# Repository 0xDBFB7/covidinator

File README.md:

# Update March 2021

Now shifted focus to purely electroporative effects. Please see

# [Pure electroporation](https://github.com/0xDBFB7/covidinator/releases/download/vx.x/pure_electroporation.pdf) 

Thanks!

---

Hi! Welcome! There's not a whole lot of real substance here, but maybe you'll find something useful. I hope you like it! 

This was a (in retrospect, misguided) project to determine if extremely high electric fields can produce mechanical stresses sufficient to break the viral membrane (so-called electroporation). This doesn't seem to be necessarily *completely* implausible, but it's sufficiently remote (and TRL 0) that I'm not super interested in continuing work on it given circumstances.

```
<3   <3   <3   <3   <3   <3   <3   <3   <3   <3   <3   <3   <3   <3 
```

# [Terse summary](https://github.com/0xDBFB7/covidinator/releases/download/vx.x/summary.pdf) 
# [Full paper with supplemental, unfinished](https://github.com/0xDBFB7/covidinator/releases/download/vx.x/paper.pdf)

## References & Resources [HTML](https://raw.githubusercontent.com/0xDBFB7/covidinator/master/documents/references.html) | [Zotero (categories!)](https://raw.githubusercontent.com/0xDBFB7/covidinator/master/documents/references.rdf) | [BiBTeX](https://raw.githubusercontent.com/0xDBFB7/covidinator/master/documents/references.bib) 

```
<:  ^_^  :>  ^_^  :>  ^_^  :>  ^_^  :>  ^_^  :>  ^_^  :>  ^_^  <:
```

Things that are here:

 * A cheap (~$300) synchronous photon counting fluorescence reader - just a crappy plate reader/Gel-Doc/spectroflurometer without the spectro- part. 
    - Can instantly quantify sub-nanogram quantities of dsDNA using Biotium GelGreen (Xu et al's fast phage titer sampling, score!).
 * Li et al's 600-picosecond avalanche transistor Marx pulser
 * A few microbiology protocols - E. coli and T4 bacteriophage.
 * A cheap (~$300) 6-12 GHz microwave absorption spectrometer / scalar network analyzer. Almost useless for small signals, does not provide the SNR required for biological purposes, don't build one.
    - firmware/eppenwolf/runs: Data from a number of data-taking runs of the Eppenwolf.
 * A wrapper around flaport/fdtd's awesome electromagnetics library:
    - tissue.py: supports import of IT.IS Foundation computational phantom voxel files, with their supplied Cole-Cole dielectric model, for tissue simulations. Pretty rough, not formally validated.
    - PCB.py: A test of coupled NGSPICE - adaptive timestep and direct KiCAD netlist import and probe/source creation. Currently totally broken.
 * biology/JAMES/ A bespoke MD program thanks to the not-invented-here syndrome. Not enough time was spent exploring GROMACS and LAMMPS features for bead-spring elastic models. A complete waste of time. There is zero reason for this to exist.
 * Reasonably bad note-taking. When all this is over I wanna make a real sweet lab notebook, the current offerings aren't, in my opinion, super great - suggestions for features and workflows are welcome!

```
<3   <3   <3   <3   <3   <3   <3   <3   <3   <3   <3   <3   <3   <3 
```

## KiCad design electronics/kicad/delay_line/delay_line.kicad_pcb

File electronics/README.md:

Milling settings:

30 degree carbide V-bit, 24 Krpm, 300 mm/min, 0.1 mm step-over, -0.1 mm step-down.

Check "Use aux. axis" in KiCAD gerber export, 

Todo: make a flatcam shell-file http://flatcam.org/manual/flatcamshell.html

G-code generated with FlatCAM, probed with Autoleveller 0.8.7 (bug in later versions),

then postprocessed with invert_probing.sh.

Board clamped to skim-cut MDF sheet and cut with regular scissors.

Paste stencils were laser cut from 80-weight black cardstock at 450 mm/min, 100%.

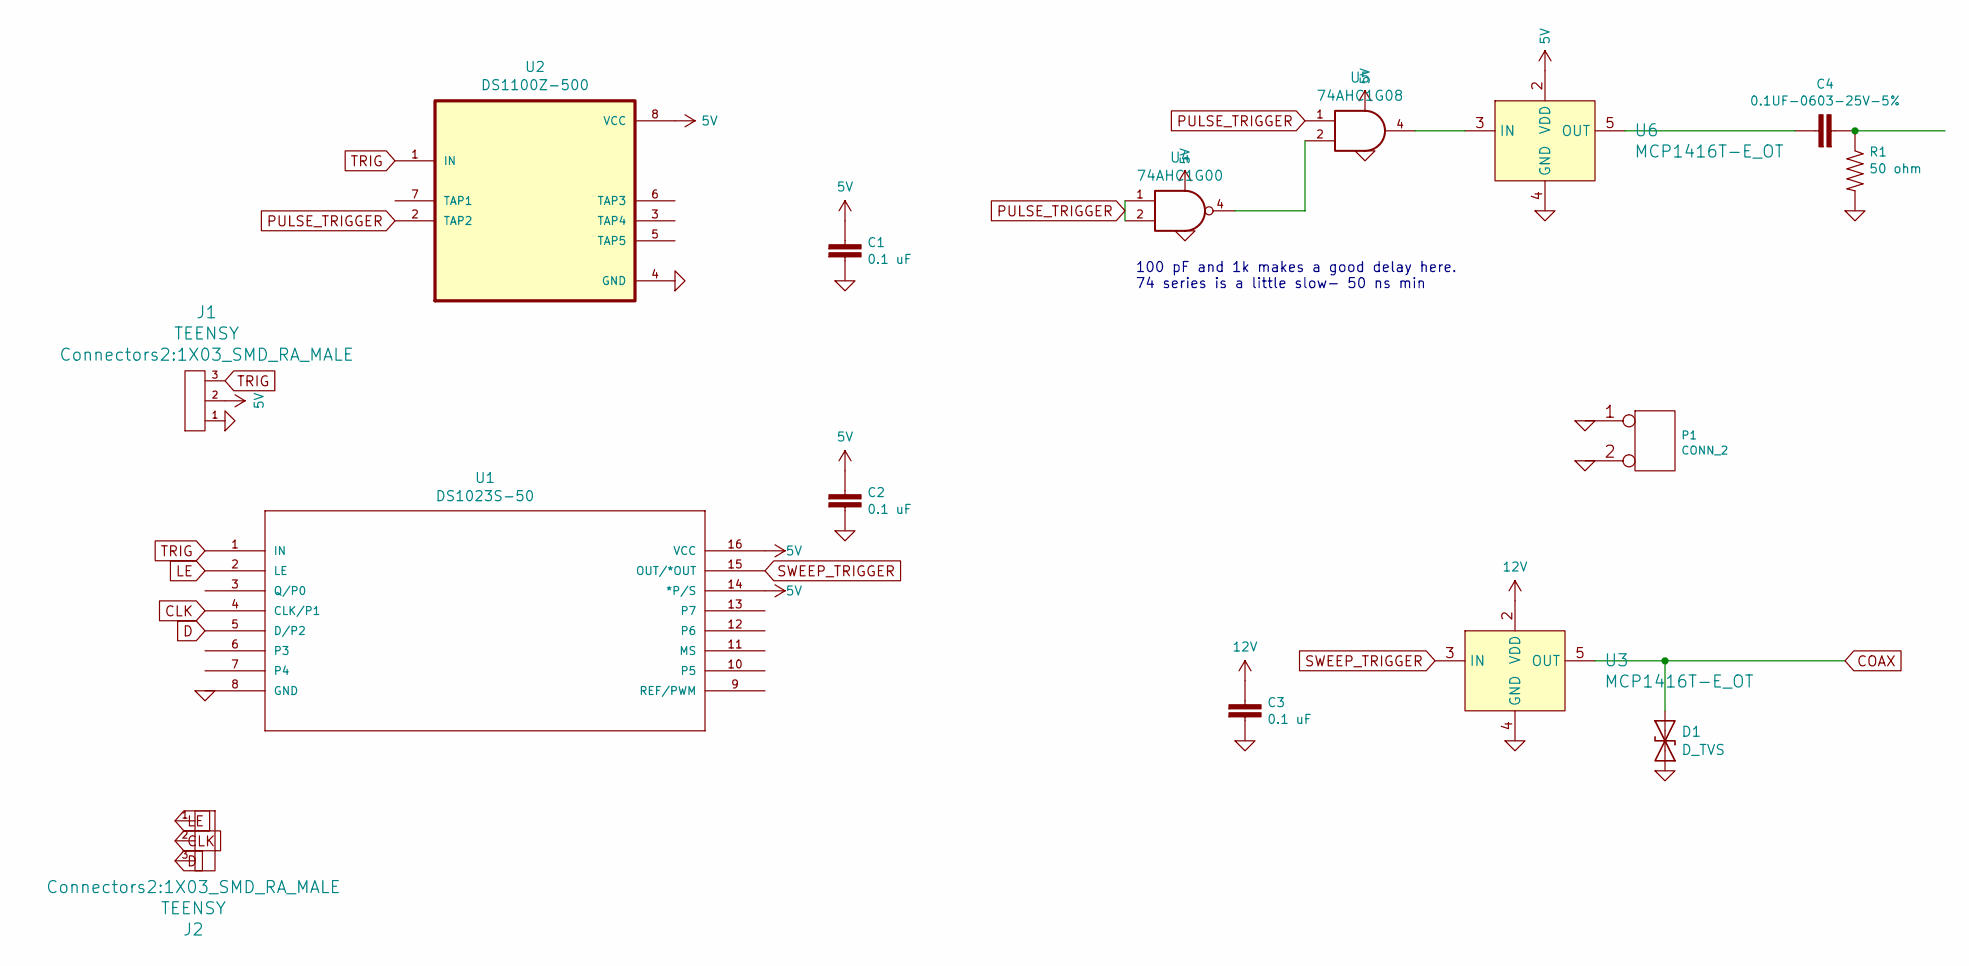
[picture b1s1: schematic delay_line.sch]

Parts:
C1, C2, C3: 0.1 uF; C_0603_1608Metric
C4: 0.1UF-0603-25V-5%; 0603
D1: D_TVS; D_SMA
J1, J2: TEENSY; 1X03_SMD_RA_MALE
P1: CONN_2; JUMPER_5102
R1: 50 ohm; 0805
U1: DS1023S-50; SOIC-16W_7.5x10.3mm_P1.27mm; MANUFACTURER_PART_NUMBER DS1023S50+
U2: DS1100Z-500; SOIC-8_3.9x4.9mm_P1.27mm
U3, U6: MCP1416T-E_OT; SOT-753; MPN MCP1416T-E/OT; Digi-Key_PN MCP1416T-E/OTCT-ND
U4: 74AHC1G00; SOT-23-5
U5: 74AHC1G08; SOT-23-5

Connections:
5V: C1.1, C2.1, J1.2, U1.14 (*P/S), U1.16 (VCC), U2.8 (VCC), U4.5 (VCC), U5.5 (VCC), U6.2 (VDD)
12V: C3.1, U3.2 (VDD)
CLK: J2.2, U1.4 (CLK/P1)
COAX: D1.1 (A1), U3.5 (OUT)
D: J2.3, U1.5 (D/P2)
GND: C1.2, C2.2, C3.2, D1.2 (A2), J1.1, P1.1, P1.2 (PM), R1.2, U1.8 (GND), U2.4 (GND), U3.4 (GND), U4.3 (GND), U5.3 (GND), U6.4 (GND)
LE: J2.1, U1.2 (LE)
unnamed: C4.1, U6.5 (OUT)
unnamed: C4.2, R1.1
unnamed: U4.4, U5.2
unnamed: U5.4, U6.3 (IN)
PULSE_TRIGGER: U2.2 (TAP2), U4.1, U4.2, U5.1
SWEEP_TRIGGER: U1.15 (OUT/*OUT), U3.3 (IN)
TRIG: J1.3, U1.1 (IN), U2.1 (IN)

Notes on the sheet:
100 pF and 1k makes a good delay here. 74 series is a little slow- 50 ns min

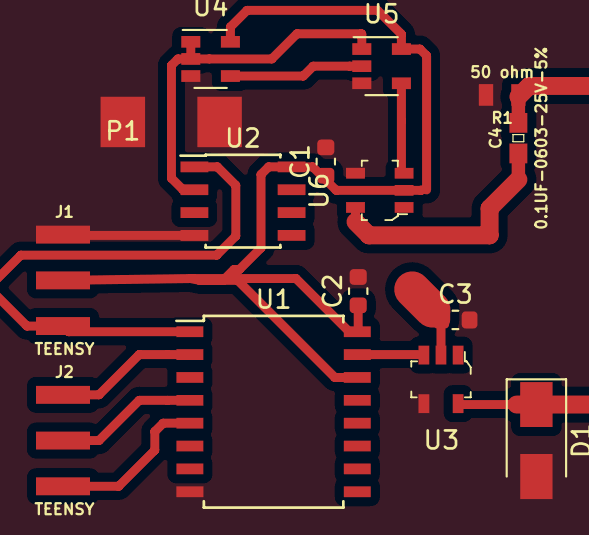
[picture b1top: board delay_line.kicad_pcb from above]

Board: 2 copper layers, 15 parts (0 on the bottom side), 14 nets.

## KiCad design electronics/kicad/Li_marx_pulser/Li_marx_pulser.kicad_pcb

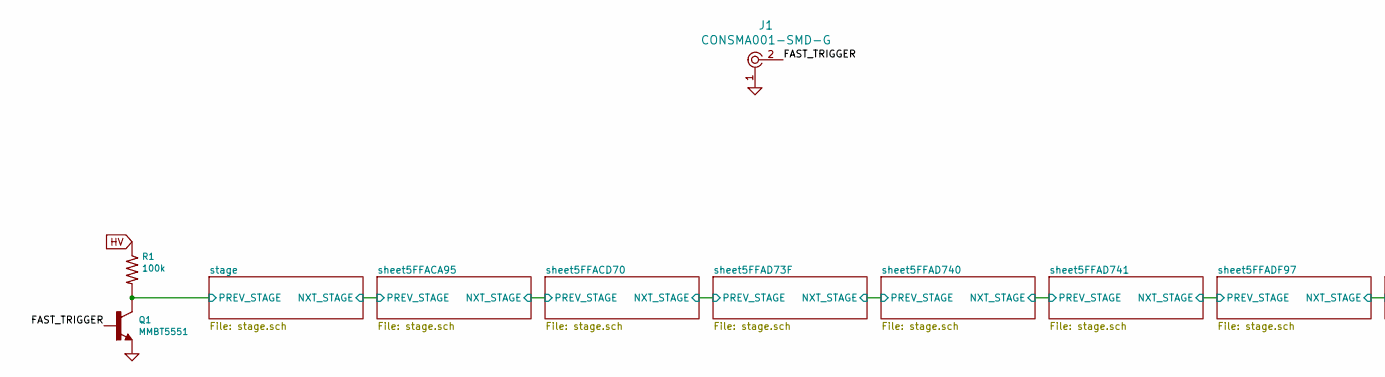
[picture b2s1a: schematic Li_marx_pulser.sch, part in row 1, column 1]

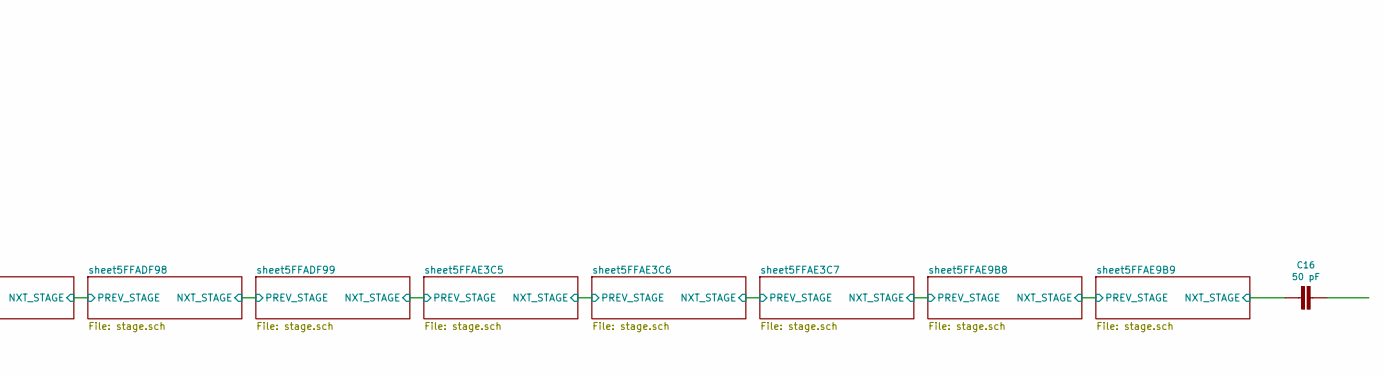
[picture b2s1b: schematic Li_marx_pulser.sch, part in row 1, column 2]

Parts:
C16: 50 pF; 1206
J1: CONSMA001-SMD-G; RF_SMA_Receptical_Vertical_CONSMA001-SMD-G; MPN CONSMA001-SMD-G; Digi-Key_PN CONSMA001-SMD-G-ND
Q1: MMBT5551; SOT23-3
R1: 100k; R_2512_6332Metric

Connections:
/FAST_TRIGGER: J1.2, Q1.1 (B)
/sheet5FFAE9B9/NXT_STAGE: C16.2; also elsewhere on the board
/stage/PREV_STAGE: Q1.3 (C), R1.2; also elsewhere on the board
GND: J1.1, Q1.2 (E); also elsewhere on the board
HV: R1.1; also elsewhere on the board

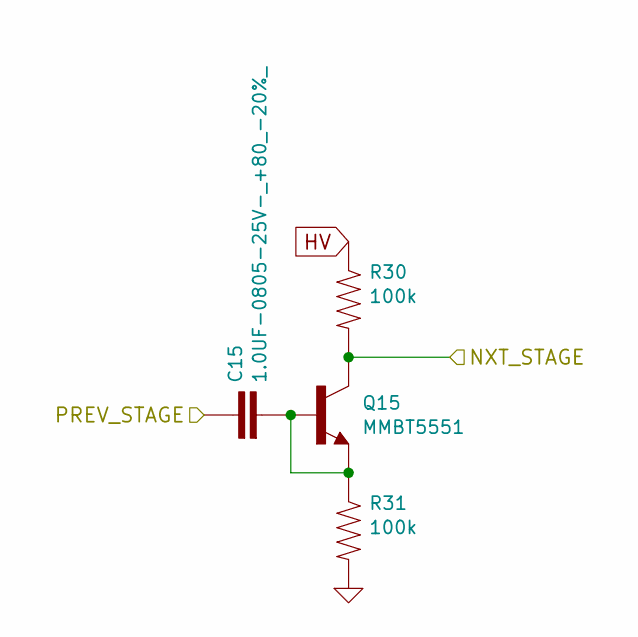
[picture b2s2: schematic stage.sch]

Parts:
C2: 1.0UF-0805-25V-_+80_-20%_; 1111(2828)
Q2: MMBT5551; SOT23-3
R4, R5: 100k; R_2512_6332Metric

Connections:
/stage/NXT_STAGE: Q2.3 (C), R4.2; also elsewhere on the board
/stage/PREV_STAGE: C2.1; also elsewhere on the board
GND: R5.2; also elsewhere on the board
HV: R4.1; also elsewhere on the board
unnamed: C2.2, Q2.1 (B), Q2.2 (E), R5.1

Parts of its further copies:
C3, C4, C5, C6, C7, C8, C9, C10, C11, C12, C13, C14, C15: 1.0UF-0805-25V-_+80_-20%_; 1111(2828)
Q3, Q4, Q5, Q6, Q7, Q8, Q9, Q10, Q11, Q12, Q13, Q14, Q15: MMBT5551; SOT23-3
R6, R7, R8, R9, R10, R11, R12, R13, R14, R15, R16, R17, R18, R19, R20, R21, R22, R23, R24, R25, R26, R27, R28, R29, R30, R31: 100k; R_2512_6332Metric

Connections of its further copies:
/sheet5FFACA95/NXT_STAGE: C4.1, Q3.3 (C), R6.2
/sheet5FFACD70/NXT_STAGE: C5.1, Q4.3 (C), R8.2
/sheet5FFAD73F/NXT_STAGE: C6.1, Q5.3 (C), R10.2
/sheet5FFAD740/NXT_STAGE: C7.1, Q6.3 (C), R12.2
/sheet5FFAD741/NXT_STAGE: C8.1, Q7.3 (C), R14.2
/sheet5FFADF97/NXT_STAGE: C9.1, Q8.3 (C), R16.2
/sheet5FFADF98/NXT_STAGE: C10.1, Q9.3 (C), R18.2
/sheet5FFADF99/NXT_STAGE: C11.1, Q10.3 (C), R20.2
/sheet5FFAE3C5/NXT_STAGE: C12.1, Q11.3 (C), R22.2
/sheet5FFAE3C6/NXT_STAGE: C13.1, Q12.3 (C), R24.2
/sheet5FFAE3C7/NXT_STAGE: C14.1, Q13.3 (C), R26.2
/sheet5FFAE9B8/NXT_STAGE: C15.1, Q14.3 (C), R28.2
/sheet5FFAE9B9/NXT_STAGE: Q15.3 (C), R30.2; also elsewhere on the board
/stage/NXT_STAGE: C3.1; also elsewhere on the board
GND: R7.2, R9.2, R11.2, R13.2, R15.2, R17.2, R19.2, R21.2, R23.2, R25.2, R27.2, R29.2, R31.2; also elsewhere on the board
HV: R6.1, R8.1, R10.1, R12.1, R14.1, R16.1, R18.1, R20.1, R22.1, R24.1, R26.1, R28.1, R30.1; also elsewhere on the board
unnamed: C3.2, Q3.1 (B), Q3.2 (E), R7.1
unnamed: C4.2, Q4.1 (B), Q4.2 (E), R9.1
unnamed: C5.2, Q5.1 (B), Q5.2 (E), R11.1
unnamed: C6.2, Q6.1 (B), Q6.2 (E), R13.1
unnamed: C7.2, Q7.1 (B), Q7.2 (E), R15.1
unnamed: C8.2, Q8.1 (B), Q8.2 (E), R17.1
unnamed: C9.2, Q9.1 (B), Q9.2 (E), R19.1
unnamed: C10.2, Q10.1 (B), Q10.2 (E), R21.1
unnamed: C11.2, Q11.1 (B), Q11.2 (E), R23.1
unnamed: C12.2, Q12.1 (B), Q12.2 (E), R25.1
unnamed: C13.2, Q13.1 (B), Q13.2 (E), R27.1
unnamed: C14.2, Q14.1 (B), Q14.2 (E), R29.1
unnamed: C15.2, Q15.1 (B), Q15.2 (E), R31.1

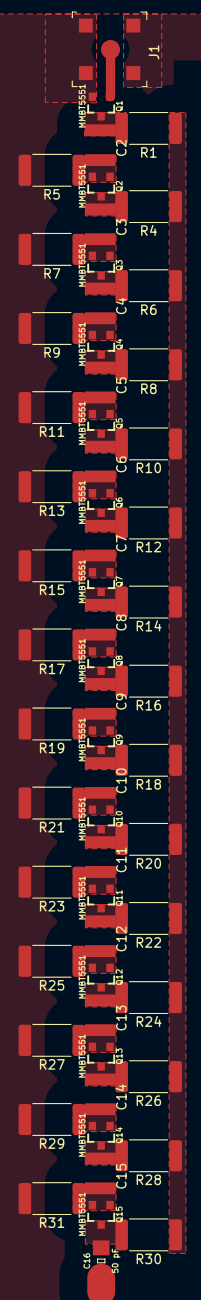
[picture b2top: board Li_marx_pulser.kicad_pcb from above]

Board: 2 copper layers, 60 parts (0 on the bottom side), 32 nets.

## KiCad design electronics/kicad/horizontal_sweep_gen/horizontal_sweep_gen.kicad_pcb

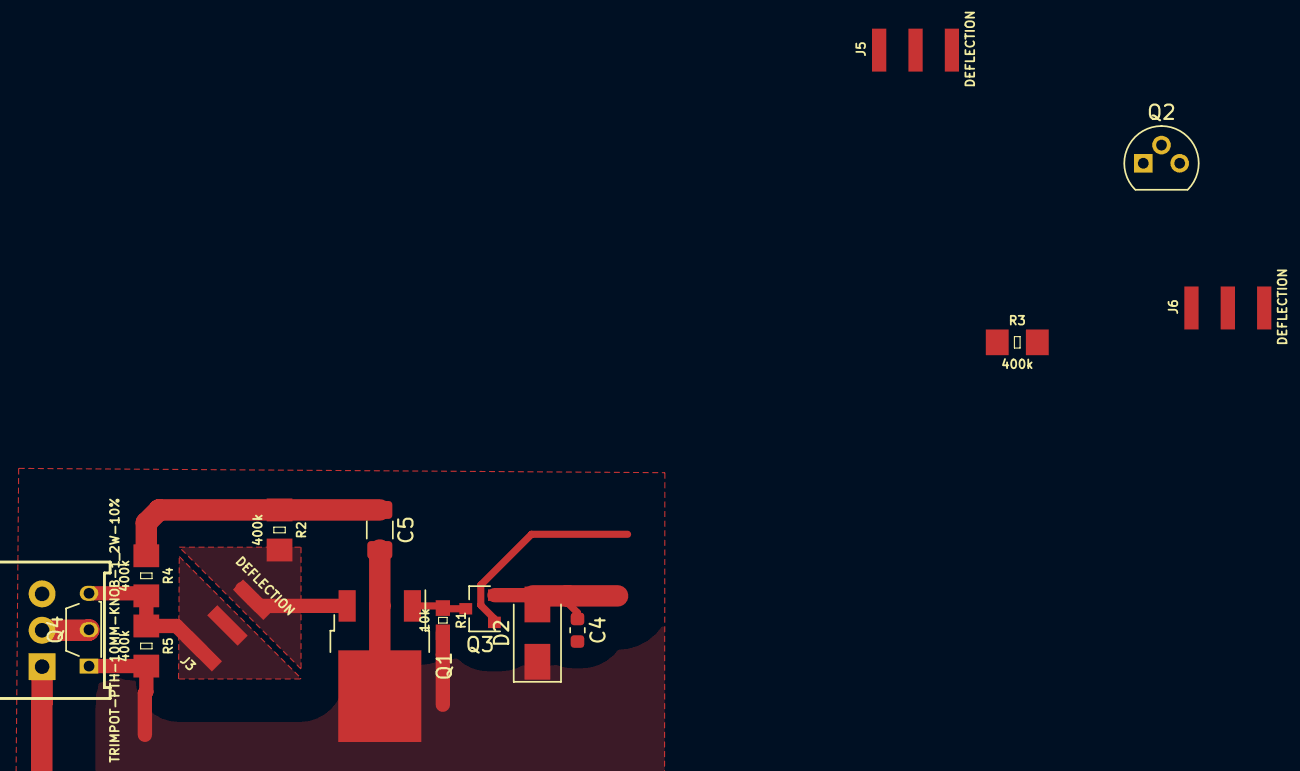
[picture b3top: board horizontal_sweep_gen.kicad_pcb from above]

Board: 2 copper layers, 16 parts (0 on the bottom side), 8 nets.

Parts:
C4: 0.1 uF; C_0603_1608Metric
C5: 50 pF; C_1206_3216Metric
D2: D_TVS; D_SMA
J3, J5, J6: DEFLECTION; 1X03_SMD_RA_MALE
Q1: TSM2N100CHC5G; TO-252-3_TabPin2
Q2: ZTX458; TO-92
Q3: BSS84; SOT-23
Q4: ZTX458; TO-92S_Wide
R1: 10k; 0603
R2, R3, R4, R5: 400k; 1206
VR1: TRIMPOT-PTH-10MM-KNOB-1_2W-10%; TRIMPOT-PTH-3386U

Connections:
GND: C4.2, C5.2, D2.1, Q1.2, Q2.1, Q4.1, R1.2, R5.2
HV: C5.1, R2.1, R4.1
HV_CENTER: J3.1, J3.2, Q4.3, R4.2, R5.1
unnamed: J5.1, Q2.3, R3.2
unnamed: Q1.1, Q3.3, R1.1
unnamed: Q4.2, VR1.2
SWEEP: J3.3, Q1.3, R2.2
VSWEEP_SLOPE: C4.1, D2.2, J6.1, Q3.2

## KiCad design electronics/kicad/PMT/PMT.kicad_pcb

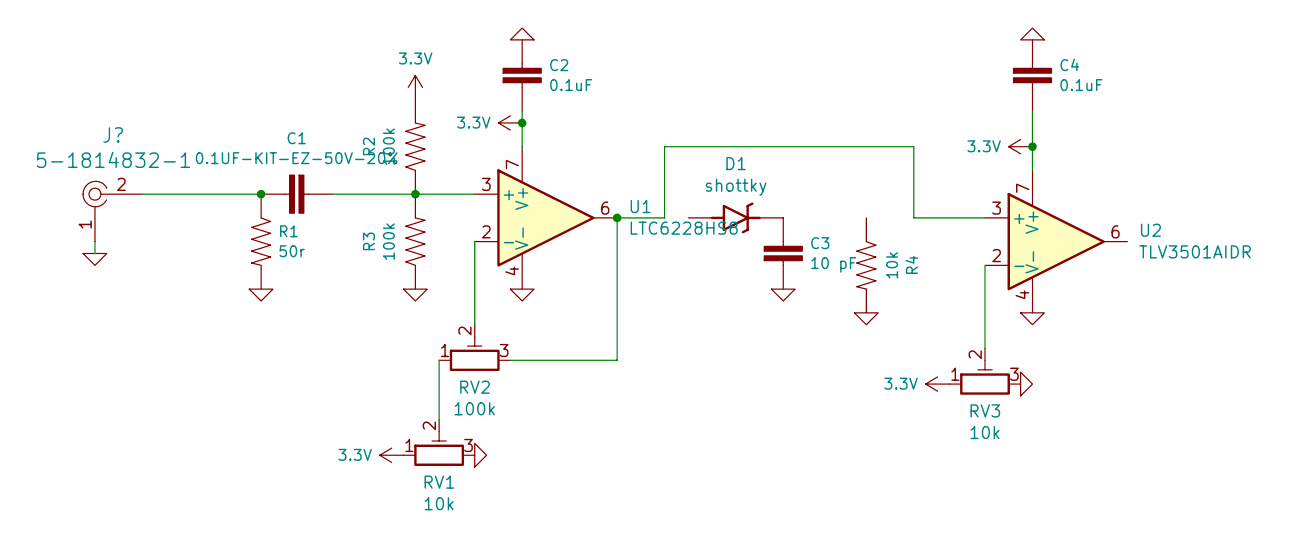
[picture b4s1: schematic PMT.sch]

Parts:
C1: 0.1UF-KIT-EZ-50V-20%; CAP-PTH-SMALL-KIT
C2, C4: 0.1uF; CAP-PTH-SMALL-KIT
C3: 10 pF; CAP-PTH-SMALL-KIT
D1: shottky; SMA-DIODE
R1: 50r; AXIAL-0.3
R2, R3: 100k; AXIAL-0.3
R4: 10k; AXIAL-0.3
RV1, RV3: 10k; PinHeader_1x03_P2.54mm_Vertical
RV2: 100k; PinHeader_1x03_P2.54mm_Vertical
U1: LTC6228HS8; DIP-8_W7.62mm
U2: TLV3501AIDR; DIP-8_W7.62mm

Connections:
3.3V: C2.2, C4.2, R2.P$2 (2), RV1.1, RV3.1, U1.7 (V+), U2.7 (V+)
GND: C2.1, C3.2, C4.1, R1.P$2 (2), R3.P$1 (1), R4.P$2 (2), RV1.3, RV3.3, U1.4 (V-), U2.4 (V-); also elsewhere on the board
unnamed: C1.1, R2.P$1 (1), R3.P$2 (2), U1.3 (+)
unnamed 3: C1.2, R1.P$1 (1); also elsewhere on the board
unnamed: C3.1, D1.C
unnamed: RV1.2, RV2.1
unnamed: RV2.2, U1.2 (-)
unnamed: RV2.3, U1.6, U2.3 (+)
unnamed: RV3.2, U2.2 (-)

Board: 2 copper layers, 15 parts (0 on the bottom side), 9 nets, no tracks yet.

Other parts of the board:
J1: 5-1814832-1; RF_SMA_Vertical_5-1814832-1

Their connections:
GND: J1.1; also elsewhere on the board
unnamed 3: J1.2; also elsewhere on the board

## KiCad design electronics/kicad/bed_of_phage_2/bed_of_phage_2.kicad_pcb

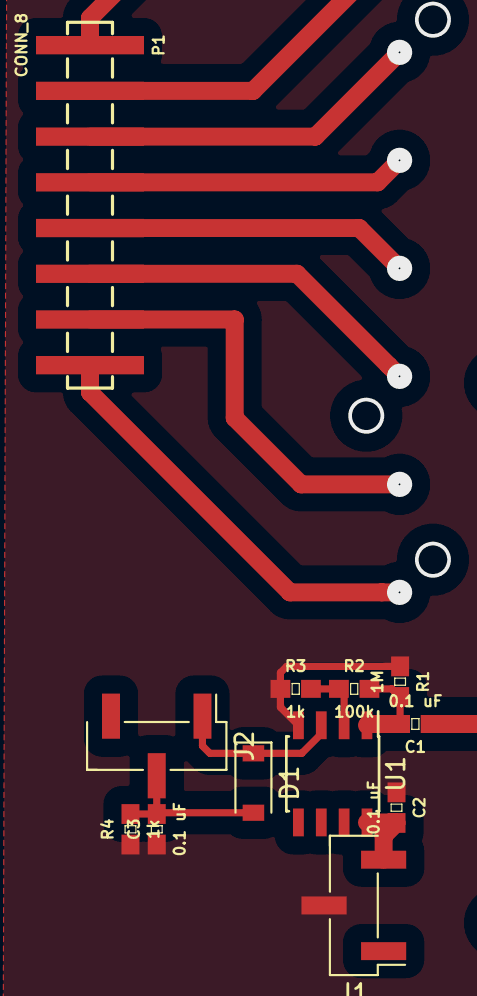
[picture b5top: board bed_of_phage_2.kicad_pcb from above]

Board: 2 copper layers, 12 parts (0 on the bottom side), 6 nets.

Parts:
C1, C2, C3: 0.1 uF; 0603
D1: SCHOTTKY; D_SOD-123
J1, J2: CONN_03; PinHeader_1x03_P2.54mm_Vertical_SMD_Pin1Left
P1: CONN_8; 1X08_SMD_MALE
R1: 1M; 0603
R2: 100k; 0603
R3, R4: 1k; 0603
U1: LM358N; SOIC-8_3.9x4.9mm_P1.27mm

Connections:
5V: C2.2, J1.3, U1.8
GND: C2.1, C3.1, J1.2, R1.1, R3.1, R4.1, U1.4
unnamed: C1.2, R1.2, R2.2, U1.1
unnamed: C3.2, D1.2, J2.2, R4.2
unnamed: D1.1, J2.1, U1.3
unnamed: R2.1, R3.2, U1.2

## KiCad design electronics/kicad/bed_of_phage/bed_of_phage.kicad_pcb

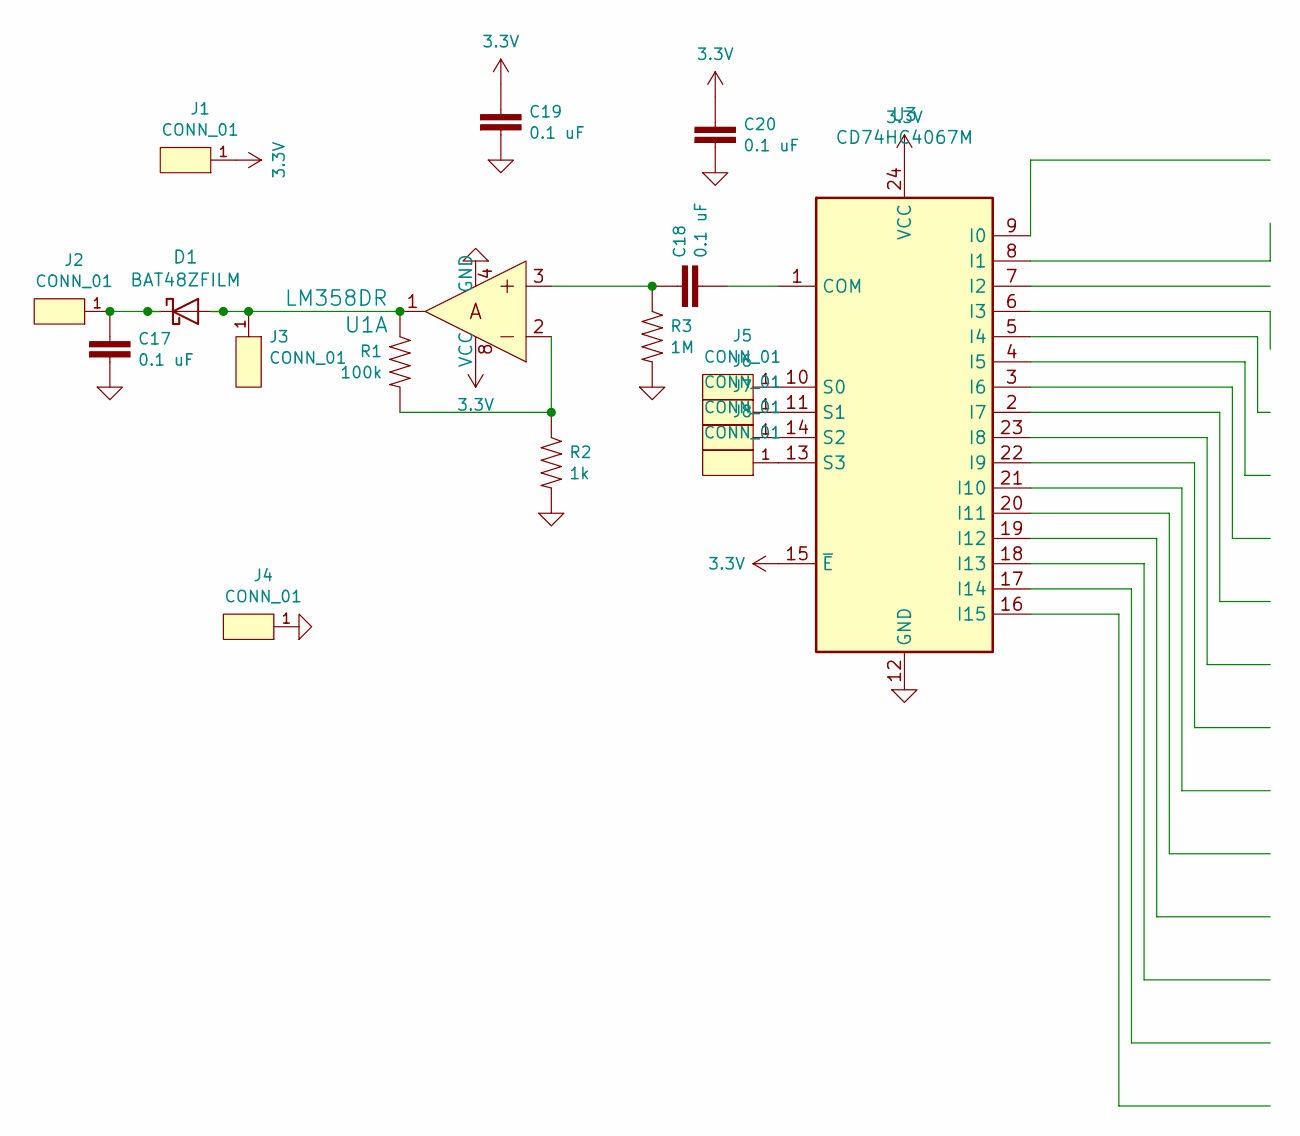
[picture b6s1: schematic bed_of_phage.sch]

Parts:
C17, C18, C19, C20: 0.1 uF; 0603
D1: BAT48ZFILM; D_SOD-123
J1, J2, J3, J4, J5, J6, J7, J8: CONN_01; 1X01
R1: 100k; 0603
R2: 1k; 0603
R3: 1M; 0603
U1: LM358DR; SOIC-8_W3.9mm; MPN LM358DR; Digi-Key_PN 296-1014-1-ND
U3: CD74HC4067M; SOIC-24W_7.5x15.4mm_P1.27mm

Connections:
3.3V: C19.1, C20.1, J1.1, U1.8 (VCC), U3.15 (~E), U3.24 (VCC)
GND: C17.2, C19.2, C20.2, J4.1, R2.2, R3.2, U1.4 (GND), U3.12 (GND)
unnamed: C17.1, D1.1 (K), J2.1
unnamed: C18.1, R3.1, U1.3
unnamed: C18.2, U3.1 (COM)
unnamed: D1.2 (A), J3.1, R1.1, U1.1
unnamed: J5.1, U3.10 (S0)
unnamed: J6.1, U3.11 (S1)
unnamed: J7.1, U3.14 (S2)
unnamed: J8.1, U3.13 (S3)
unnamed: R1.2, R2.1, U1.2

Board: 2 copper layers, 18 parts (0 on the bottom side), 11 nets, no tracks yet.

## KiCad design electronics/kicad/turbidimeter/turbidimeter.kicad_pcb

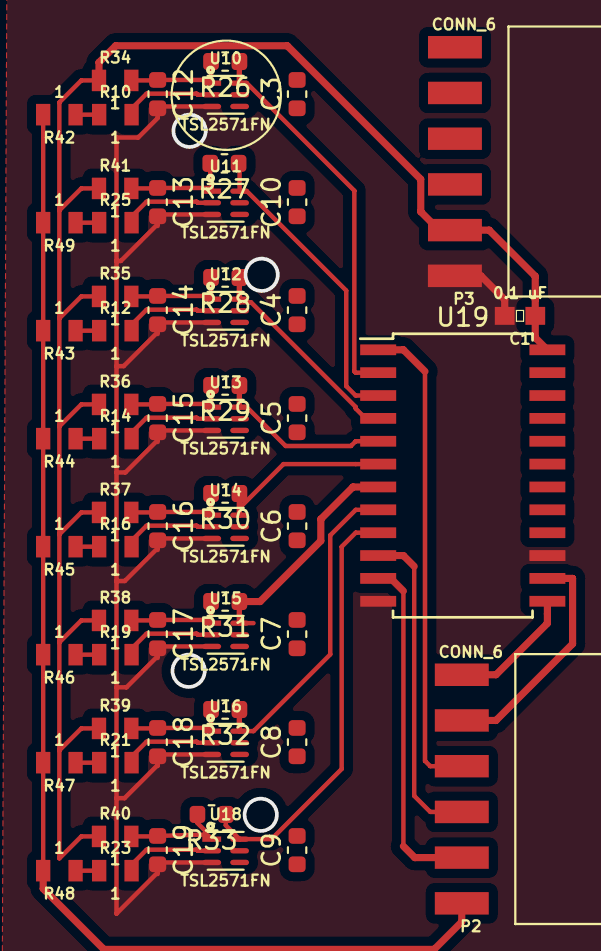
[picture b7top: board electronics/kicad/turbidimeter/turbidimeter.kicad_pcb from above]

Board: 2 copper layers, 60 parts (0 on the bottom side), 40 nets.

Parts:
C1: 0.1 uF; 0603
C3, C4, C5, C6, C7, C8, C9, C10, C12, C13, C14, C15, C16, C17, C18, C19: 0.1 uF; C_0603_1608Metric
P2, P3: CONN_6; 1X06-SMD-FEMALE
R10, R12, R14, R16, R19, R21, R23, R25, R34, R35, R36, R37, R38, R39, R40, R41, R42, R43, R44, R45, R46, R47, R48, R49: 1; 0805
R26, R27, R28, R29, R30, R31, R32, R33: 10k; R_0603_1608Metric
U10, U11, U12, U13, U14, U15, U16, U18: TSL2571FN; DFN-6-2X2
U19: CD74HC4067M; SOIC-24W_7.5x15.4mm_P1.27mm

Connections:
3.3V: C1.1, P3.5, R34.1, R35.1, R36.1, R37.1, R38.1, R39.1, R40.1, R41.1, U19.24
/S0: R33.1, U18.6, U19.9
/S1: R32.1, U16.6, U19.8
/S2: R31.1, U15.6, U19.7
/S3: R30.1, U14.6, U19.6
/S4: R29.1, U13.6, U19.5
/S5: R28.1, U12.6, U19.4
/S6: R27.1, U11.6, U19.3
/S7: R26.1, U10.6, U19.2
A0: P2.5, U19.11
A1: P2.4, U19.10
A2: P2.2, U19.14
A3: P2.1, U19.13
GND: C1.2, C12.2, C13.2, C14.2, C15.2, C16.2, C17.2, C18.2, C19.2, P3.6, U10.3, U11.3, U12.3, U13.3, U14.3, U15.3, U16.3, U18.3, U19.12, U19.15
unnamed: C12.1, R26.2, R34.2, U10.1
unnamed: C13.1, R27.2, R41.2, U11.1
unnamed: C14.1, R28.2, R35.2, U12.1
unnamed: C15.1, R29.2, R36.2, U13.1
unnamed: C16.1, R30.2, R37.2, U14.1
unnamed: C17.1, R31.2, R38.2, U15.1
unnamed: C18.1, R32.2, R39.2, U16.1
unnamed: C19.1, R33.2, R40.2, U18.1
unnamed: R10.1, R42.1
unnamed: R10.2, U10.2
unnamed: R12.1, R43.1
unnamed: R12.2, U12.2
unnamed: R14.1, R44.1
unnamed: R14.2, U13.2
unnamed: R16.1, R45.1
unnamed: R16.2, U14.2
unnamed: R19.1, R46.1
unnamed: R19.2, U15.2
unnamed: R21.1, R47.1
unnamed: R21.2, U16.2
unnamed: R23.1, R48.1
unnamed: R23.2, U18.2
unnamed: R25.1, R49.1
unnamed: R25.2, U11.2
SCL: P2.6, R42.2, R43.2, R44.2, R45.2, R46.2, R47.2, R48.2, R49.2
SDA: P2.3, U19.1

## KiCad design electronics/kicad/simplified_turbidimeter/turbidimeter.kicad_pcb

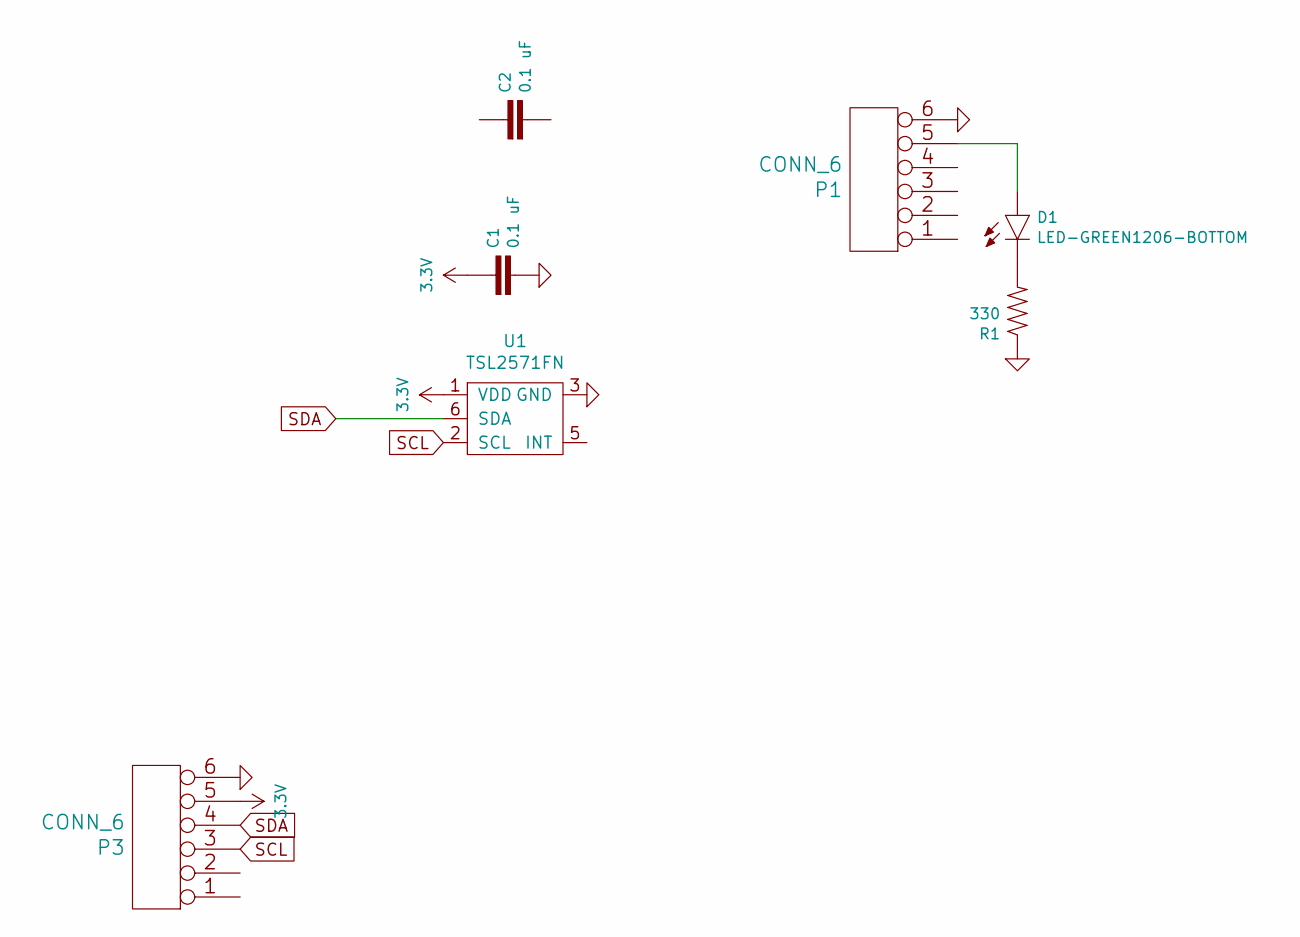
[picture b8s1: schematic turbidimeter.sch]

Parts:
C1, C2: 0.1 uF; C_0603_1608Metric
D1: LED-GREEN1206-BOTTOM; LED-1206-BOTTOM
P1, P3: CONN_6; 1X06-SMD-FEMALE
R1: 330; R_0603_1608Metric
U1: TSL2571FN; DFN-6-2X2

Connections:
3.3V: C1.1, P3.5, U1.1 (VDD)
GND: C1.2, P1.6, P3.6, R1.1, U1.3 (GND)
unnamed: D1.A, P1.5
unnamed: D1.C, R1.2
SCL: P3.3, U1.2 (SCL)
SDA: P3.4, U1.6 (SDA)

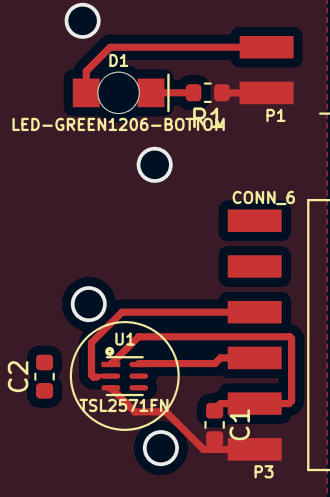
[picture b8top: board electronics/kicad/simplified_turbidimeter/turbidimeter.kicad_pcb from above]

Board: 2 copper layers, 7 parts (0 on the bottom side), 6 nets.

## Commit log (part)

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2020-08-31 Phage run 1
2020-08-31 Shows something amazing, but let's be very careful; this could all be thermal
2020-09-01 Data from the first run is probably spurious.
2020-09-01 Fixed 'far' sensor by re-adding shorted AC-coupling cap after double
2020-09-01 Power
2020-09-02 Silicone cap test
2020-09-02 I think everything's ready?
2020-09-02 Working on firmware
2020-09-03 Making sure pulse is as described
2020-09-04 Quick ol' FDTD sim of lung
2020-09-04 Here we go
2020-09-04 Run 2
2020-09-05 Again, very pretty graph, but we must temper our emotions.
2020-09-05 Preparing for run 3
2020-09-06 More prep
2020-09-06 fdtd
2020-09-06 Teensy died in the middle of the test.
2020-09-06 Test 3 complete
2020-09-06 Turbidity 1!
2020-09-06 Turbidity 1, engaininated
2020-09-07 Turbidity N+1
2020-09-07 Turbidity N+2
2020-09-07 Forgot that some were flipped
2020-09-07 An idea.
2020-09-07 Preparing for test 4
2020-09-07 More prep for t4
2020-09-07 Verified that pulses are as described
2020-09-07 Prepping for 4 still
2020-09-07 Generated slide
2020-09-08 nooope
2020-09-08 Bunch of simulations, bunch of garbage
2020-09-09 Turbidimeter actually working now
2020-09-09 Culturing a whole crapload of bacteria
2020-09-09 Assay still didn't work! Darnit!
2020-09-10 Drum shaker thing
2020-09-10 Wonderful turbidimeter
2020-09-10 finally
2020-09-11 turbidimeter
2020-09-11 Agar
2020-09-11 Pouring agars
2020-09-13 Slide 0
2020-09-14 Impedance
2020-09-14 Screwed up a simple op-amp circuit
2020-09-14 nope, I didn't screw that up.
2020-09-15 test 1
2020-09-17 test
2020-09-17 Personal device
2020-09-18 Soliton 1
2020-09-20 Stuff and things
2020-09-20 Wrote a better abstract
2020-09-21 text
2020-09-21 Maxima
2020-09-22 Words
2020-09-24 Little progress
2020-09-25 meeeeeep
2020-09-27 fuck fucking fucking fucker
2020-09-27 beta glo next assay
2020-09-29 tests
2020-09-30 hail
2020-10-05 Propagation
2020-10-07 More propagation
2020-10-08 Stuff
2020-10-09 Protein charges processed
2020-10-09 Charge and molecular weights
2020-10-10 lab notebook note
2020-10-12 Propagation?
2020-10-12 Fourier series
2020-10-13 testing
2020-10-15 Prep for run 5, fresh supplies
2020-10-15 T4r+ is a mutant of T4r, not the other way 'round. darnit darnit darnit gosh darn darnit
2020-10-16 Experiment 2
2020-10-19 propagator
2020-10-19 Reconstruction just fine
2020-10-21 Photometric paper - wow! Amazing! Should have done this!
2020-10-22 Gelgreen
2020-10-24 Apparent success
2020-10-24 Run 5 prep
2020-10-25 More run 5 prep.
2020-10-25 Run 5 slide 0
2020-10-25 Fixed PWM again, slide 0 re-done
2020-10-25 green corrections
2020-10-26 Green correction factors
2020-10-26 470 nm led
2020-10-29 Correction
2020-11-03 Fluorescnece
2020-11-04 pmt counter
2020-11-05 Synchronizing FPGA
2020-11-05 Functioning lock-in
2020-11-06 Functional FPGA counter
2020-11-06 race condition?
2020-11-06 glitch still somehow present
2020-11-06 TCL dump
2020-11-07 Fluor. working great
2020-11-09 Probe dump
2020-11-09 Fixed erratic bug
2020-11-10 Fluores. improvements
2020-11-10 Disabled sweep
2020-11-10 Slide 1 and fluro for run 6
2020-11-11 trying quadrature
2020-11-11 Removing quadrature, adding time-correlated
2020-11-11 IQ viewer
2020-11-11 Time-correlated working great
2020-11-11 screw it
2020-11-11 just not working out.
2020-11-12 Going to replicate but conventionally
2020-11-12 overwrote a bunch of data, reverting
2020-11-12 CAUTION
2020-11-12 disregard
2020-11-12 Slide 0 fluro. data
2020-11-12 data analysis mistake, conclusions are wrong
2020-11-12 no data
2020-11-15 capillary
2020-11-15 Tube 0
2020-11-15 Tube 3
2020-11-15 Tube 3 done
2020-11-15 fuck
2020-11-15 fuck fuck fuck fuck fuck fuck fuck fuck fuckfuck fuck fuck fuck fuck fuck fuck fuck
2020-11-15 Tube 7
2020-11-15 nice and consistent.
2020-11-17 Moving experiment logs out of protocols/pulse.pnw
2020-11-18 data
2020-11-18 Run 9
2020-11-18 basic run done
2020-11-19 more testing
2020-11-19 Increased pulse peak voltage
2020-11-19 documenting the change
2020-11-20 done
2020-11-20 still nothing
2020-11-20 deadly power
2020-11-20 snap?
2020-11-20 nah.
2020-11-21 Wording
2020-11-21 more charge section words
2020-11-22 osmotically-stressed phage doesn't do it either
2020-11-22 writing!
2020-11-24 Writing
2020-11-25 Huh, viscous damping works out
2020-11-25 Microfluidic channel
2020-11-26 Wooords
2020-11-27 Optimal control
2020-11-29 No analytic solution
2020-12-02 math
2020-12-11 Replicated Z,C's result using functionalDerivative! yay
2020-12-12 Apparent success?
2020-12-13 lipidwrapping
2020-12-13 BUMPy proteins!
2020-12-14 Got lazy, doing it numerically
2020-12-15 Basinhopper yet again!
2020-12-15 Prop working, GF not yet
2020-12-15 fucker
2020-12-15 just a scale issue
2020-12-15 Apparent success with water, let's try muscle
2020-12-15 Cole-Cole - sawtooth wave looked on Debye
2020-12-15 yay apparently solved?
2020-12-16 Writing notes
2020-12-16 Liposome test
2020-12-17 liposome
2020-12-18 Liposome!
2020-12-18 Vesicle centering...
2020-12-18 waater box
2020-12-18 Minimization
2020-12-18 Minimizing again!
2020-12-19 Minimization succesful
2020-12-19 Water minim. now
2020-12-19 LINCS warnings
2020-12-19 fucker!
2020-12-19 Yay liposomes!
2020-12-19 Sim pipeline working great - no electrostatic effect yet,
2020-12-19 VMD signal library
2020-12-20 TRAVIS
2020-12-20 TRAVIS has zero pad, thank you very much to the lovely people
2020-12-20 Fixed travis zero pad
2020-12-20 Plotting
2020-12-20 Thicker water layer
2020-12-21 No effects.
2020-12-21 Some actual resonance!
2020-12-21 Going to add non-equilibrium MD
2020-12-22 Let's use restraint...
2020-12-22 Restraints cause lipid buckling
2020-12-23 Prep for CG NCoV model and also drag constant
2020-12-23 Rotating liposome to determine drag
2020-12-26 "Prompt" electroporation
2021-01-04 scd5000 import?
2021-01-07 fuckeradfkljaldkf jaldskfj fuck fuck fuck fuck
2021-01-08 scan converter, but fucking why
2021-01-09 marx pulser design
2021-01-10 Horizontal amplifier
2021-01-11 pdftex
2021-01-11 Writing, re-organizing references
2021-01-13 scan-converter
2021-01-17 Progress
2021-01-18 Pulse generator
2021-01-19 why's fdtd broken?
2021-01-19 Microfluidic coplanar waveguide sim
2021-01-19 Bug in a bunch of sims, might have affected the result
2021-01-19 still broken sources
2021-01-19 for some reason it depends on dt?
2021-01-20 definitely fixed now.
2021-01-20 Pulse generator functional
2021-01-21 Coplanar exposure cell working
2021-01-21 Added gaussian functions
2021-01-22 Delay line functioning great
2021-01-23 Dialogue
2021-01-23 I find a bug in prop_num_optimize
2021-01-24 Fixed.
2021-01-24 More discussion
2021-01-24 Building the thing
2021-01-26 Progress on RPi cal
2021-01-26 gearing up for the test
2021-01-26 fucker fucking fucking fucking fucking fucking fucking fucking fucking fucking
2021-01-26 No dice. Reorganized.
2021-01-28 dammit the precursor's at the wrong frequency
2021-01-28 all data is questionable; autosampler was right fucked fuck fuck fuck fuck fuck fuck fuck fuck fuck fuck fuck fuck fuck fuck fuck fuck fuck fuck
2021-01-28 idiot
2021-01-28 Brillouin cleanups
2021-01-29 gosh darnit
2021-01-31 goddamnit, going down the same path again...
2021-01-31 Poisson boltzmann
2021-02-01 delphi
2021-02-01 what the fuck am I doing? what the fuck?
2021-02-01 MEDUSA
2021-02-03 Restructuring, maybe?
2021-02-09 Text and prop improvements
2021-02-10 Oh hey the brilluoin just had a bug
2021-02-11 log colorbar
2021-02-11 Rotation
2021-02-17 Tersenating
2021-02-17 whatever
2021-02-18 More progress on summary
2021-02-19 readme
2021-02-20 edits
2021-02-22 More edits
2021-02-26 Ruler
2021-03-01 Tersenating again
2021-03-04 Fields put in data table
2021-03-05 More work on writing, need to add pulse counts
2021-03-06 Removed README disclaimer
2021-03-08 Adding supplemental
2021-03-12 Rewording text slightly in case biorxiv is a good idea
2021-03-14 Screw it, let's try liposomes
2021-03-21 Pure electroporation
2021-03-22 Pulse stacking - charge-pulse!!!!!
2021-03-22 electroporation
2021-03-27 Transmembrane library
2021-03-28 More transmembrane library
2021-03-28 Want to add debye later
2021-03-28 Transmembrane
2021-03-29 Triangle wave works
2021-03-29 Bug!
2021-04-02 Rectangular pulses - trapezoid still not working properly
2021-04-04 differential
2021-04-06 kotnik
2021-04-07 Talele
2021-04-08 Fiiine I'll do it numerically
2021-04-08 Convolution working properly
2021-04-08 fft division doesn't seem to work
2021-04-09 fft subtratction
2021-04-09 fairly decent results
2021-04-09 Even better results
2021-04-11 attempt at a bang-bang control scheme
2021-04-12 Using a real optimal control software
2021-04-13 Convert to differential equation
2021-04-14 Some work on the paper wording
2021-04-15 DoF error
2021-04-15 Whoops, wrong transfer function!
2021-04-16 Oops, switched terms again
2021-04-16 GEKKO DE seems to be working now
2021-04-16 optimization isn't quite working however
2021-04-16 did that just work?
2021-04-16 Nope just a glitch :(((
2021-04-16 Taking PSOPT for a spin
2021-04-17 More PSOPT
2021-04-18 rk4 integrator
2021-04-18 got it in one
2021-04-18 Integral constraint failing?
2021-04-18 Fixed bug introduced
2021-04-18 PSOPT constants calculation
2021-04-18 nope, something's gone wrong
2021-04-18 Fixed test propagate control derivative scaling
2021-04-19 Apparent success once again?
2021-04-19 Another possible solution
2021-04-19 fixed floating derivatives
2021-04-19 Oh man, now that's a messy function! no wonder we're having convergence issues
2021-04-19 everything's broken
2021-04-19 Using LLNL-ANSI lpopt
2021-04-19 this is taking forever
2021-04-19 good lord it's done
2021-04-20 Switched from spral to HSL now that I got the email
2021-04-20 Some stability
2021-04-20 best one yet, "only" 1/50
2021-04-20 satisfactory solution
2021-04-20 1/36, pretty effective!
2021-04-20 1/20 - slightly better
2021-04-20 12! A really crazy shape, too!
2021-04-20 6.9, really great, but weird glitches
2021-04-21 Very large problem size
2021-04-24 julia DDP
2021-04-26 iLQR
2021-04-26 iLQR apparently working, though not yielding any useful result yet
2021-04-27 Spinning off fdtd into submodule
2021-04-27 Spun off fdtd extensions
2021-04-27 fixed broken link
2021-04-28 1/2 possibly?
2021-04-28 1.3!
2021-04-28 Last three tests are bunk because of wrong values
2021-04-28 nondimensionalization might be the key
2021-04-29 Unicode math notetaking?!
2021-04-30 further nondimensionalization
2021-04-30 Wrong values nondimen.
2021-04-30 Version 2 of nondimensionalized
2021-04-30 nondimensionalizing isn't working
2021-05-04 Returned home
2021-05-04 PSOPT seems to converge very stably now that nondimen. is being used
2021-05-04 Promising
2021-05-04 starting to get somewhere!
2021-05-04 1/6!
2021-05-05 A possible analytic method?
2021-05-07 Kwim's awesome
2021-05-07 Testing analytic control solution
2021-05-08 I don't fucking understand any fucking thing motherfucking fuck fuck fuck fuck fuck fuck fuck fuck fuck fuck
2021-05-08 I'm such a fucking idiot, everything is different, the fucking equations are different wtf
2021-05-08 Different
2021-05-17 Musings on detection in wastewater
2021-05-19 An obvious discrepancy
2021-05-20 Coefficients reversed for some reason!?!
2021-05-20 Swapped terms on virus_optimize.cxx, still no idea why
2021-05-20 swapped terms on gekko_nondimensionalized, now there's no convergence at all?
2021-05-21 Apparently eliminated artifactual pulses
2021-05-21 most promising yet
2021-05-23 Simplifications & munging code
2021-05-24 A lack of substance
2021-05-25 Apparently successful solution - except doesn't validate!
2021-05-25 success
2021-05-27 Introduced a bug somewhere
2021-05-31 Found a bug in virus_optimize
2021-05-31 another apparent success, but again it doesn't validate
2021-05-31 again, good solution, doesn't validate
2021-05-31 Trying out u0 control on virus_optimize
2021-06-02 functioning derivative
2021-06-03 Performance of derivative-taking much improved
2021-06-05 holoborodko's smooth differential stencils
2021-06-06 symbolic output solution is useless
2021-06-06 Trying Differential Evolution
2021-06-10 Pretty graphs
2021-06-11 Hampath
2021-06-17 Hampath math notes
2021-06-22 Gradient bang-bang switching time method, and perhaps Fourier method
2021-06-26 Working on Nagurka
